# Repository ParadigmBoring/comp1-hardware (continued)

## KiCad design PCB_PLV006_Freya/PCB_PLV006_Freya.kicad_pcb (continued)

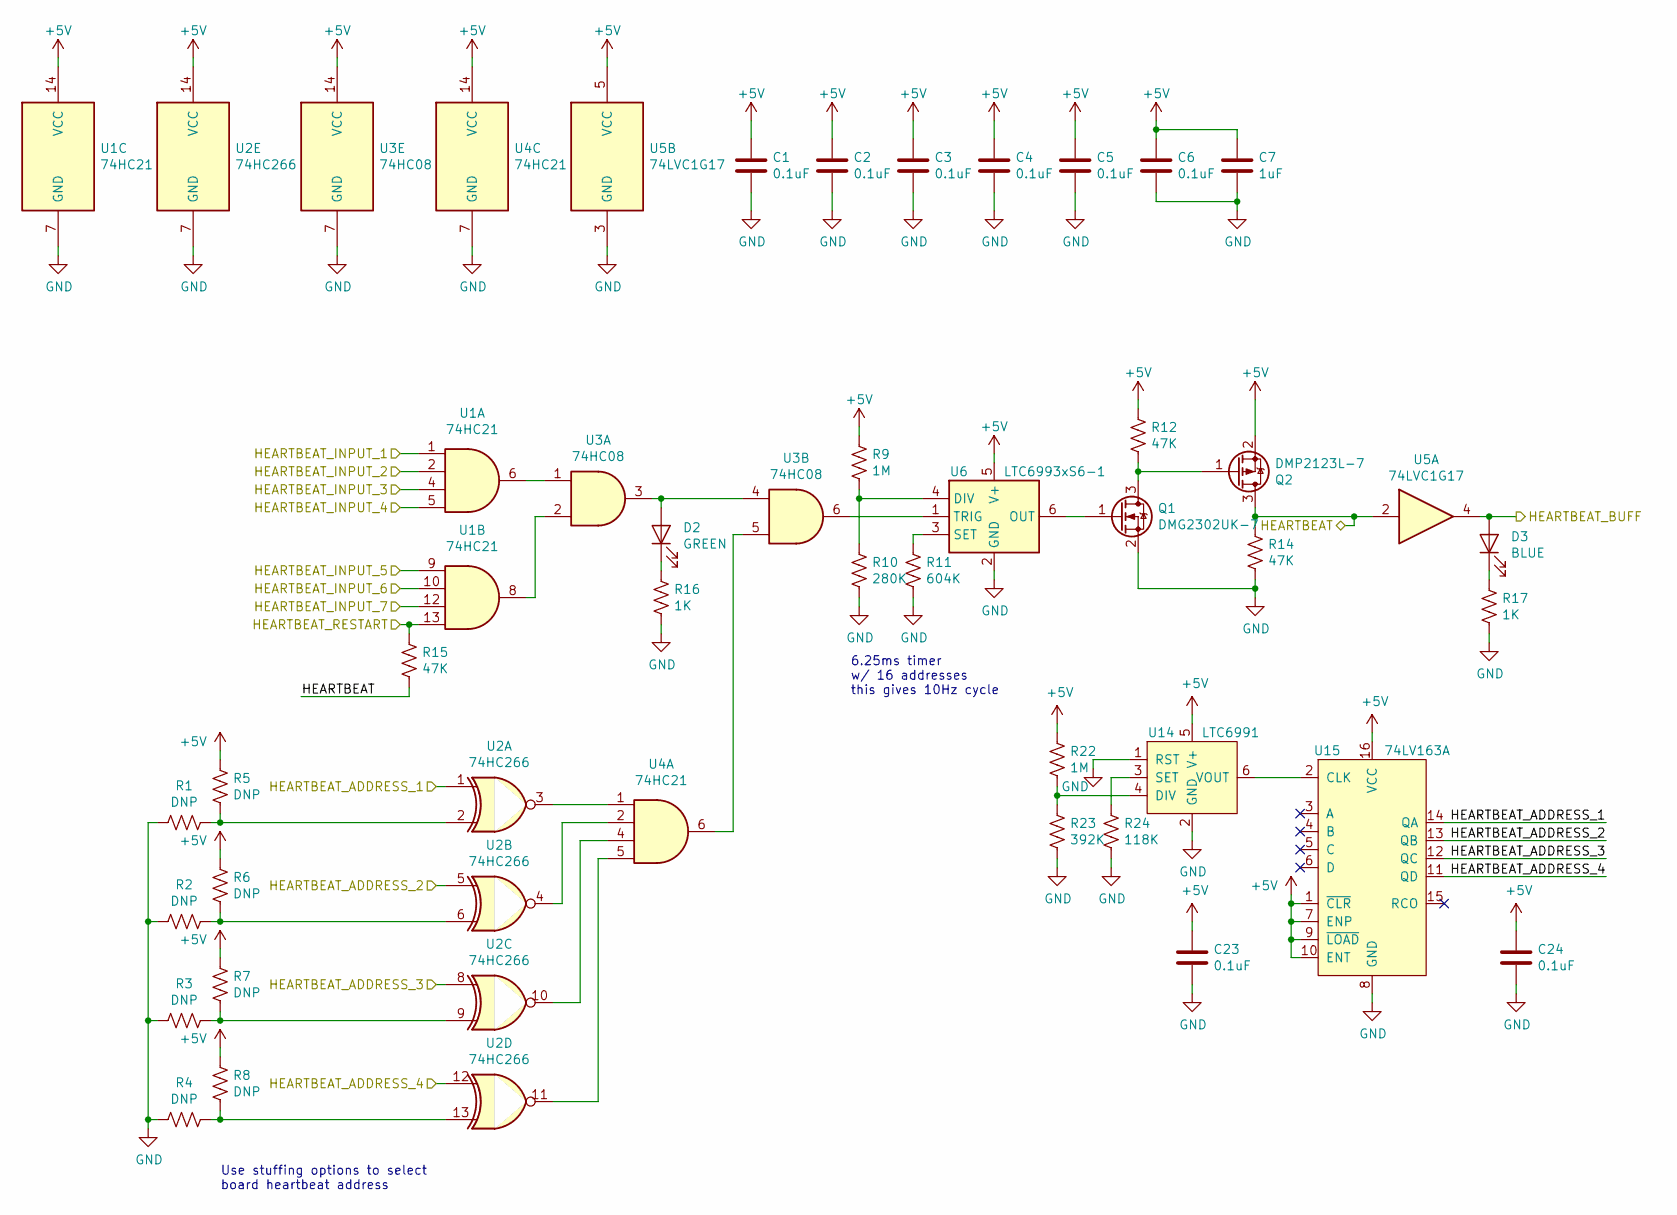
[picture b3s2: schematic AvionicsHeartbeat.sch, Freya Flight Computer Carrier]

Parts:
C1, C2, C3, C4, C5, C6: 0.1uF; C_0603_1608Metric_Pad1.05x0.95mm_HandSolder; Digikey 311-1341-1-ND
C7: 1uF; C_0603_1608Metric_Pad1.05x0.95mm_HandSolder
C23, C24: 0.1uF; C_0603_1608Metric_Pad1.05x0.95mm_HandSolder
D2: GREEN; LED_0805_2012Metric_Pad1.15x1.40mm_HandSolder; Digikey 732-4983-1-ND
D3: BLUE; LED_0805_2012Metric_Pad1.15x1.40mm_HandSolder; Digikey 732-4982-1-ND
Q1: DMG2302UK-7; SOT-23_Handsoldering; Digikey DMG2302UK-7DICT-ND
Q2: DMP2123L-7; SOT-23_Handsoldering; Digikey DMP2123LDICT-ND
R1, R2, R3, R4, R5, R6, R7, R8: DNP; R_0603_1608Metric_Pad1.05x0.95mm_HandSolder
R9, R22: 1M; R_0603_1608Metric_Pad1.05x0.95mm_HandSolder
R10: 280K; R_0603_1608Metric_Pad1.05x0.95mm_HandSolder
R11: 604K; R_0603_1608Metric_Pad1.05x0.95mm_HandSolder
R12, R14, R15: 47K; R_0603_1608Metric_Pad1.05x0.95mm_HandSolder
R16, R17: 1K; R_0603_1608Metric_Pad1.05x0.95mm_HandSolder
R23: 392K; R_0603_1608Metric_Pad1.05x0.95mm_HandSolder
R24: 118K; R_0603_1608Metric_Pad1.05x0.95mm_HandSolder
U1, U4: 74HC21; SOIC-14_3.9x8.7mm_P1.27mm; Digikey 296-31574-1-ND
U2: 74HC266; SOIC-14_3.9x8.7mm_P1.27mm; Digikey 296-31804-1-ND
U3: 74HC08; SOIC-14_3.9x8.7mm_P1.27mm; Digikey 296-14506-1-ND
U5: 74LVC1G17; SOT-23-5_HandSoldering; Digikey 296-11933-1-ND
U6: LTC6993xS6-1; TSOT-23-6; Digikey LTC6993CS6-1#TRMPBFCT-ND
U14: LTC6991; TSOT-23-6_HandSoldering
U15: 74LV163A; SOIC-16_3.9x9.9mm_P1.27mm

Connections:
+5V: C1.1, C2.1, C3.1, C4.1, C5.1, C6.1, C7.1, C23.1, C24.1, Q2.2 (S), R5.1, R6.1, R7.1, R8.1, R9.1, R12.1, R22.1, U1.14 (VCC), U2.14 (VCC), U3.14 (VCC), U4.14 (VCC), U5.5 (VCC), U6.5 (V+), U14.5 (V+), U15.1 (~CLR~), U15.7 (ENP), U15.9 (~LOAD~), U15.10 (ENT), U15.16 (VCC); also elsewhere on the board
/AvionicsHeartbeatTemplate/HEARTBEAT_INPUT_3: U1.4; also elsewhere on the board
/AvionicsHeartbeatTemplate/HEARTBEAT_INPUT_4: U1.5; also elsewhere on the board
/AvionicsHeartbeatTemplate/HEARTBEAT_INPUT_5: U1.9; also elsewhere on the board
/AvionicsHeartbeatTemplate/HEARTBEAT_INPUT_6: U1.10; also elsewhere on the board
/AvionicsHeartbeatTemplate/HEARTBEAT_INPUT_7: U1.12; also elsewhere on the board
/HEARTBEAT_ADDRESS_1: U2.1, U15.14 (QA); also elsewhere on the board
/HEARTBEAT_ADDRESS_2: U2.5, U15.13 (QB); also elsewhere on the board
/HEARTBEAT_ADDRESS_3: U2.8, U15.12 (QC); also elsewhere on the board
/HEARTBEAT_ADDRESS_4: U2.12, U15.11 (QD); also elsewhere on the board
/HEARTBEAT_RESTART: R15.1, U1.1, U1.13; also elsewhere on the board
/MCU_QB_INPUT: U1.2; also elsewhere on the board
/QB: Q2.3 (D), R14.1, R15.2, U5.2; also elsewhere on the board
/QB_BUFF: D3.2 (A), U5.4; also elsewhere on the board
GND: C1.2, C2.2, C3.2, C4.2, C5.2, C6.2, C7.2, C23.2, C24.2, Q1.2 (S), R1.1, R2.1, R3.1, R4.1, R10.2, R11.2, R14.2, R16.2, R17.2, R23.2, R24.2, U1.7 (GND), U2.7 (GND), U3.7 (GND), U4.7 (GND), U5.3 (GND), U6.2 (GND), U14.1 (RST), U14.2 (GND), U15.8 (GND); also elsewhere on the board
unnamed: D2.1 (K), R16.1
unnamed: D2.2 (A), U3.3, U3.4
unnamed: D3.1 (K), R17.1
unnamed: Q1.1 (G), U6.6 (OUT)
unnamed: Q1.3 (D), Q2.1 (G), R12.2
unnamed: R1.2, R5.2, U2.2
unnamed: R2.2, R6.2, U2.6
unnamed: R3.2, R7.2, U2.9
unnamed: R4.2, R8.2, U2.13
unnamed: R9.2, R10.1, U6.4 (DIV)
unnamed: R11.1, U6.3 (SET)
unnamed: R22.2, R23.1, U14.4 (DIV)
unnamed: R24.1, U14.3 (SET)
unnamed: U1.6, U3.1
unnamed: U1.8, U3.2
unnamed: U2.3, U4.1
unnamed: U2.4, U4.2
unnamed: U2.10, U4.4
unnamed: U2.11, U4.5
unnamed: U3.5, U4.6
unnamed: U3.6, U6.1 (TRIG)
unnamed: U14.6 (VOUT), U15.2 (CLK)

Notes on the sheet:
6.25ms timer w/ 16 addresses this gives 10Hz cycle
Use stuffing options to select board heartbeat address

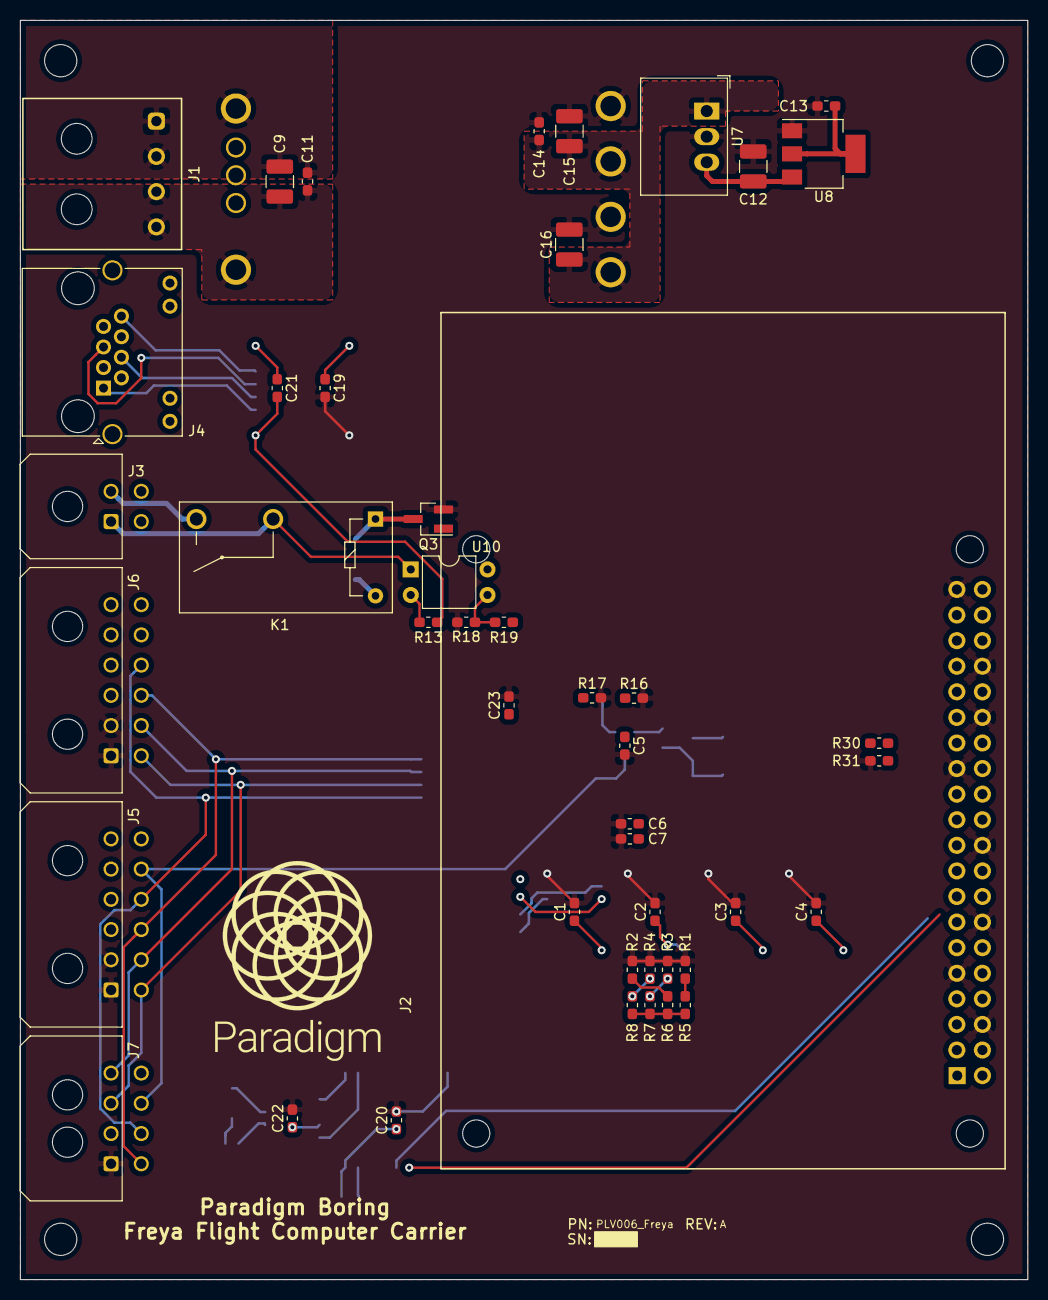
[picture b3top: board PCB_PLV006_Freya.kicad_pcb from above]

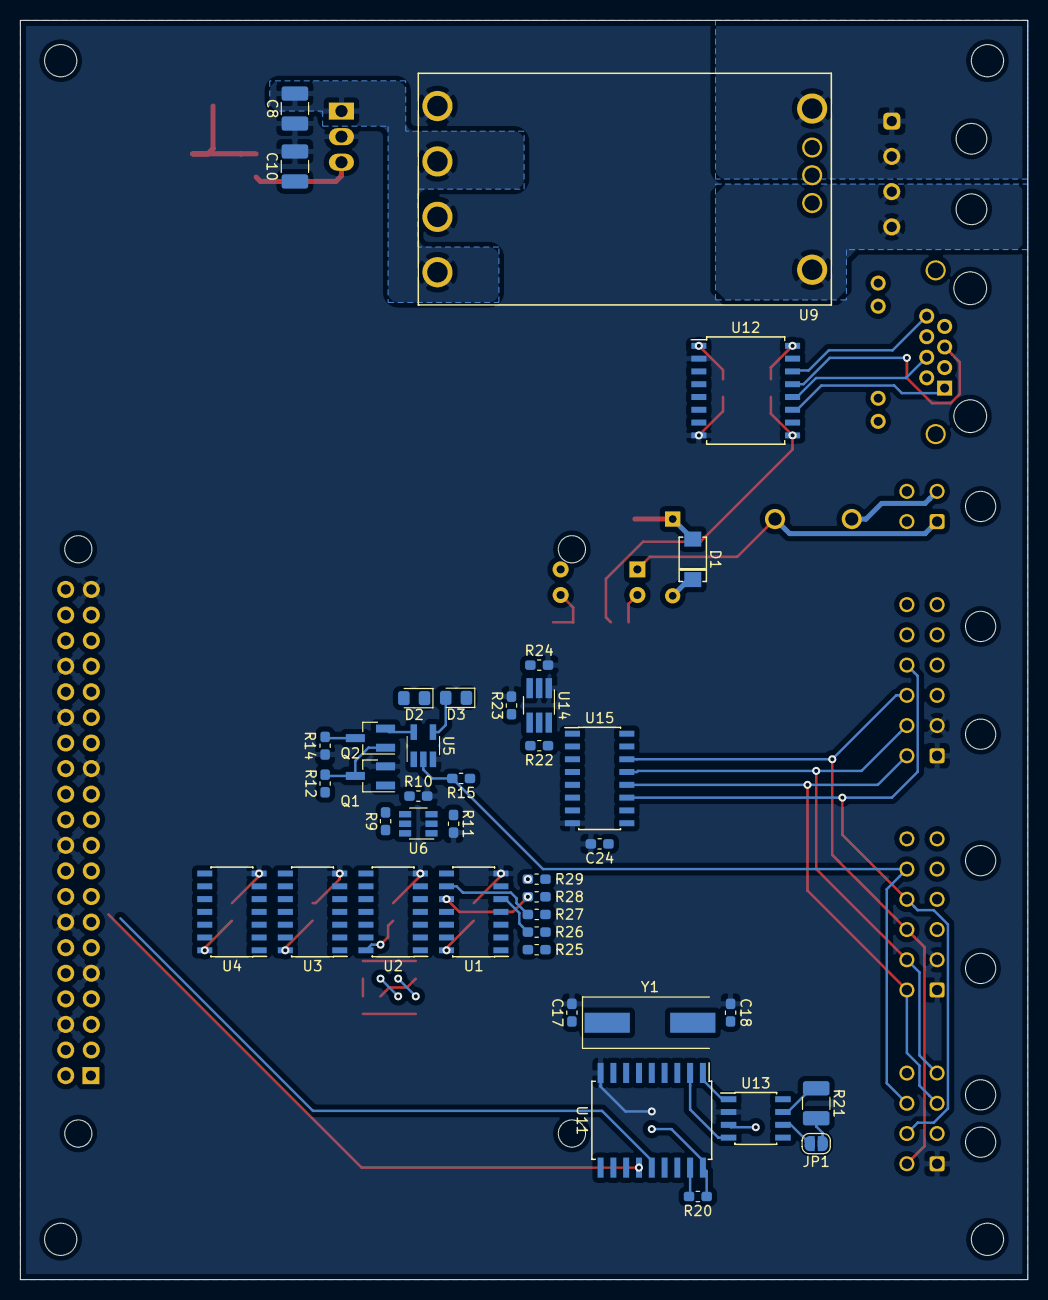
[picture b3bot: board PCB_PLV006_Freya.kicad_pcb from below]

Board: 2 copper layers, 100.0 x 125.0 mm, 86 parts (40 on the bottom side), 68 nets.

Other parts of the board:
J5: NAV; Molex_Micro-Fit_3.0_43045-1200_2x06_P3.00mm_Horizontal
J6: SENSE/ACT; Molex_Micro-Fit_3.0_43045-1200_2x06_P3.00mm_Horizontal
J7: QBI; Molex_Micro-Fit_3.0_43045-0800_2x04_P3.00mm_Horizontal

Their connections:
+24V: J5.3, J5.4, J6.3, J6.4, J7.2; also elsewhere on the board
/CANH: J5.6, J6.6; also elsewhere on the board
/CANL: J5.5, J6.5; also elsewhere on the board
/HEARTBEAT_ADDRESS_1: J5.9, J6.9, J7.5; also elsewhere on the board
/HEARTBEAT_ADDRESS_2: J5.8, J6.8, J7.4; also elsewhere on the board
/HEARTBEAT_ADDRESS_3: J5.7, J6.7, J7.3; also elsewhere on the board
/HEARTBEAT_ADDRESS_4: J5.10, J6.10, J7.6; also elsewhere on the board
/QB: J5.11, J6.11, J7.7; also elsewhere on the board
GND: J5.1, J5.2, J6.1, J6.2, J7.1; also elsewhere on the board

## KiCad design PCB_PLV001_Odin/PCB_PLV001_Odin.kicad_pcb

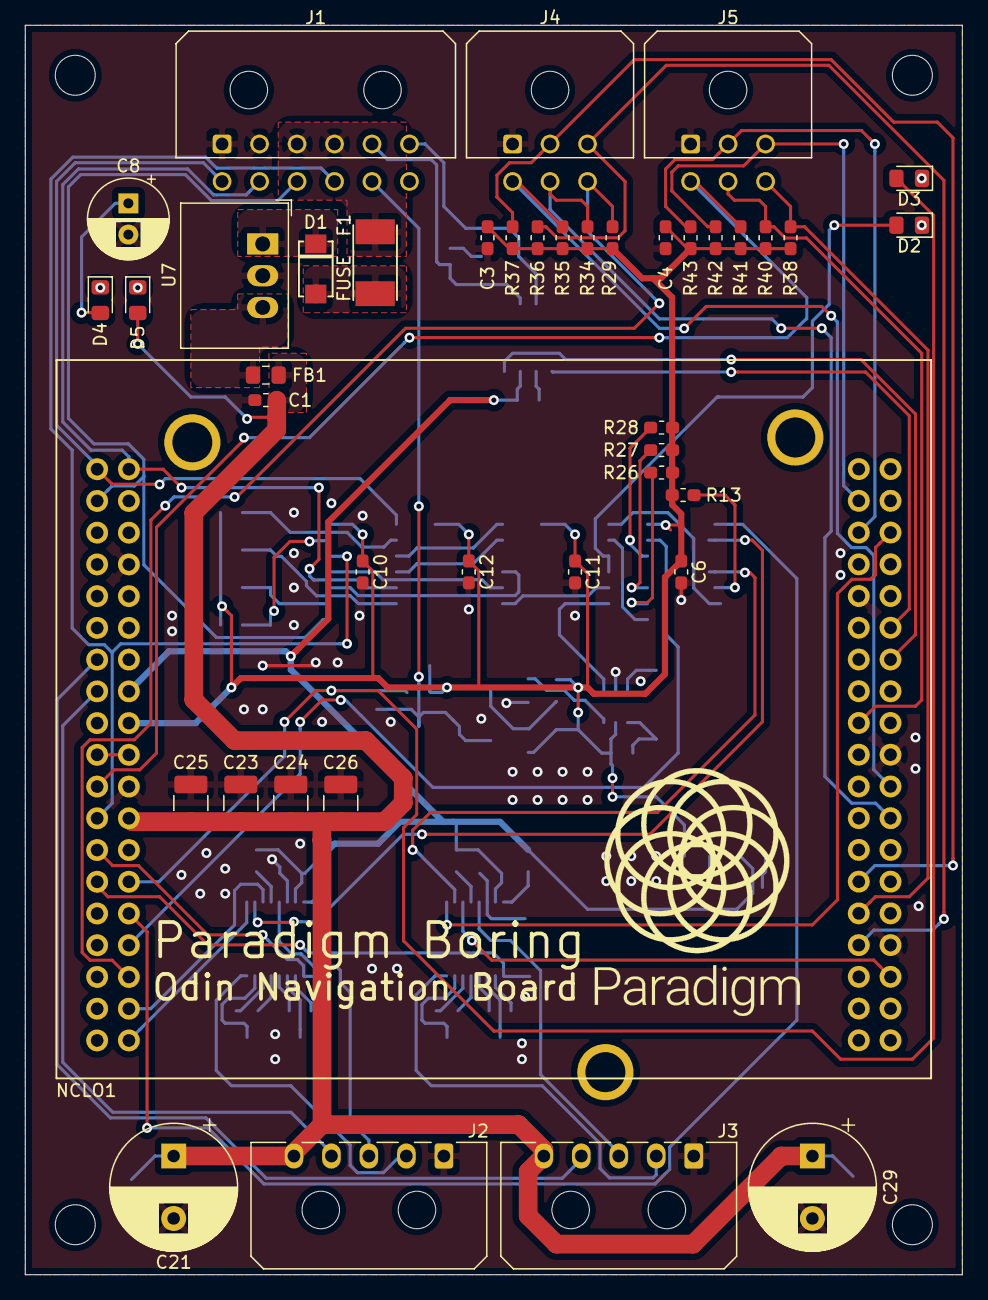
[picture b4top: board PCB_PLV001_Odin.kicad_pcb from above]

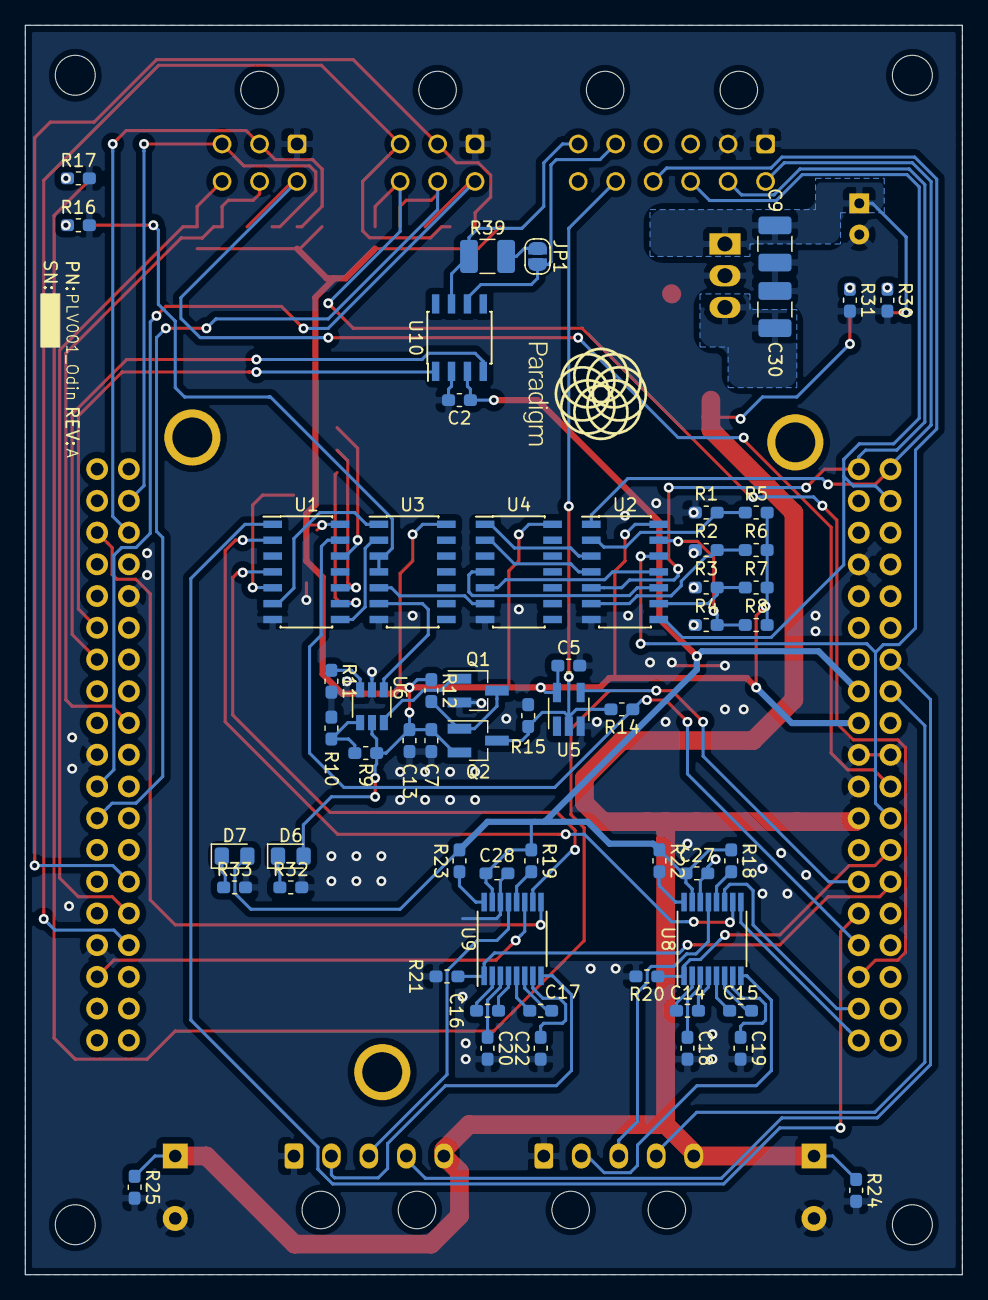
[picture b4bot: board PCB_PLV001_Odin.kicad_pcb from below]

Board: 2 copper layers, 75.0 x 100.0 mm, 101 parts (59 on the bottom side), 88 nets.

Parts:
C1, C2, C3, C4, C5, C6, C10, C11, C12, C13, C14, C15, C16, C17, C18, C19, C20, C22, C27, C28: 0.1uF; C_0603_1608Metric_Pad1.05x0.95mm_HandSolder
C7: 1uF; C_0603_1608Metric_Pad1.05x0.95mm_HandSolder
C8: 47uF; CP_Radial_D6.3mm_P2.50mm
C9, C23, C24, C25, C26, C30: 10uF; C_1210_3225Metric_Pad1.42x2.65mm_HandSolder
C21, C29: 470uF; CP_Radial_D10.0mm_P5.00mm
D1: D_Schottky; DO-221AC
D2: QB_IN; LED_0805_2012Metric_Pad1.15x1.40mm_HandSolder
D3: QB_OUT; LED_0805_2012Metric_Pad1.15x1.40mm_HandSolder
D4: VIN; LED_0805_2012Metric_Pad1.15x1.40mm_HandSolder
D5: 12V; LED_0805_2012Metric_Pad1.15x1.40mm_HandSolder
D6: 5V; LED_0805_2012Metric_Pad1.15x1.40mm_HandSolder
D7: 3V3; LED_0805_2012Metric_Pad1.15x1.40mm_HandSolder
F1: 2A; BelFuse_0679H
FB1: 30ohm@100MHz; L_0805_2012Metric_Pad1.15x1.40mm_HandSolder
J1: PWR/CAN/QB; Molex_Micro-Fit_3.0_43045-1200_2x06_P3.00mm_Horizontal
J2: IMU; Molex_Micro-Fit_3.0_43650-0500_1x05_P3.00mm_Horizontal
J3: INS; Molex_Micro-Fit_3.0_43650-0500_1x05_P3.00mm_Horizontal
J4: ROT1; Molex_Micro-Fit_3.0_43045-0600_2x03_P3.00mm_Horizontal
J5: ROT2; Molex_Micro-Fit_3.0_43045-0600_2x03_P3.00mm_Horizontal
JP1: CAN_TERM; SolderJumper-2_P1.3mm_Open_RoundedPad1.0x1.5mm
NCLO1: NUCLEO-L476RG; ST_Nucleo-64
Q1: DMG2302UK-7; SOT-23_Handsoldering
Q2: DMP2123L-7; SOT-23_Handsoldering
R1, R2, R3, R4, R5, R6, R7, R8: DNP; R_0603_1608Metric_Pad1.05x0.95mm_HandSolder
R9: 1M; R_0603_1608Metric_Pad1.05x0.95mm_HandSolder
R10: 280K; R_0603_1608Metric_Pad1.05x0.95mm_HandSolder
R11: 604K; R_0603_1608Metric_Pad1.05x0.95mm_HandSolder
R12, R14, R15, R20, R21: 47K; R_0603_1608Metric_Pad1.05x0.95mm_HandSolder
R13, R18, R19, R22, R23, R26, R27, R28: 0; R_0603_1608Metric_Pad1.05x0.95mm_HandSolder
R16, R17, R32: 1K; R_0603_1608Metric_Pad1.05x0.95mm_HandSolder
R24, R25: 100K; R_0603_1608Metric_Pad1.05x0.95mm_HandSolder
R29, R34, R35, R36, R37, R38, R40, R41, R42, R43: 10K; R_0603_1608Metric_Pad1.05x0.95mm_HandSolder
R30: 11K; R_0603_1608Metric_Pad1.05x0.95mm_HandSolder
R31: 4.7K; R_0603_1608Metric_Pad1.05x0.95mm_HandSolder
R33: 47; R_0603_1608Metric_Pad1.05x0.95mm_HandSolder
R39: 120; R_1210_3225Metric_Pad1.42x2.65mm_HandSolder
U1, U4: 74HC21; SOIC-14_3.9x8.7mm_P1.27mm
U2: 74HC266; SOIC-14_3.9x8.7mm_P1.27mm
U3: 74HC08; SOIC-14_3.9x8.7mm_P1.27mm
U5: 74LVC1G17; SOT-23-5_HandSoldering
U6: LTC6993xS6-1; TSOT-23-6
U7: R-78B12-2.0; Converter_DCDC_RECOM_R-78B-2.0_THT
U8, U9: MAX3221; TSSOP-16_4.4x5mm_P0.65mm
U10: SN65HVD232; SOIC-8_3.9x4.9mm_P1.27mm

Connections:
+3V3: C2.1, C27.1, C28.1, D7.2, NCLO1.16, R18.1, R19.1, R22.1, R23.1, U8.15, U9.15, U10.3
+5V: C3.1, C4.1, C5.1, C6.1, C7.1, C10.1, C11.1, C12.1, C13.1, D6.2, NCLO1.18, Q2.2, R5.1, R6.1, R7.1, R8.1, R9.1, R12.1, R13.2, R26.2, R27.2, R28.2, R29.2, R34.2, R35.2, R36.2, R37.2, R38.2, R40.2, R41.2, R42.2, R43.2, U1.14, U2.14, U3.14, U4.14, U5.5, U6.5
+12V: C1.1, C21.1, C23.1, C24.1, C25.1, C26.1, C29.1, D5.2, FB1.1, J2.5, J3.5, NCLO1.24, R24.1, R25.1
+24V: C8.1, C9.1, D1.1, D4.2, U7.1
/232_1_VALID: U1.2, U8.10
/232_2_VALID: U1.4, U9.10
/AvionicsHeartbeatTemplate/HEARTBEAT_INPUT_4: R13.1, U1.5
/AvionicsHeartbeatTemplate/HEARTBEAT_INPUT_5: R26.1, U1.9
/AvionicsHeartbeatTemplate/HEARTBEAT_INPUT_6: R27.1, U1.10
/AvionicsHeartbeatTemplate/HEARTBEAT_INPUT_7: R28.1, U1.12
/CANH: J1.6, R39.1, U10.7
/CANL: J1.5, JP1.2, U10.6
/CAN_RX: NCLO1.52, U10.4
/CAN_TX: NCLO1.50, U10.1
/HEARTBEAT: J1.11, Q2.3, R14.2, R15.1, U5.2
/HEARTBEAT_ADDRESS_1: J1.7, NCLO1.1, U2.1
/HEARTBEAT_ADDRESS_2: J1.8, NCLO1.2, U2.5
/HEARTBEAT_ADDRESS_3: J1.9, NCLO1.3, U2.8
/HEARTBEAT_ADDRESS_4: J1.10, NCLO1.23, U2.12
/HEARTBEAT_BUFF: D3.2, NCLO1.28, U5.4
/HEARTBEAT_RESTART: NCLO1.32, R14.1, U1.13
/IMU_TOV: J2.4, NCLO1.15
/INS_PPS: J3.4, NCLO1.13
/MCU_QB_INPUT: NCLO1.30, U1.1
/ROT1_PPS1: J4.2, NCLO1.65, R37.1
/ROT1_PPS2: J4.3, NCLO1.69, R36.1
/ROT1_PPS3: J4.4, NCLO1.60, R35.1
/ROT1_PPS4: J4.5, NCLO1.62, R34.1
/ROT1_PPS5: J4.6, NCLO1.34, R29.1
/ROT2_PPS1: J5.2, NCLO1.43, R43.1
/ROT2_PPS2: J5.3, NCLO1.41, R42.1
/ROT2_PPS3: J5.4, NCLO1.21, R41.1
/ROT2_PPS4: J5.5, NCLO1.55, R40.1
/ROT2_PPS5: J5.6, NCLO1.67, R38.1
/Transceivers/232_1_RX: J2.2, U8.8
/Transceivers/232_1_TX: J2.3, U8.13
/Transceivers/232_2_RX: J3.2, U9.8
/Transceivers/232_2_TX: J3.3, U9.13
/UART1_RX: NCLO1.38, U8.9
/UART1_TX: NCLO1.36, U8.11
/UART2_RX: NCLO1.44, U9.9
/UART2_TX: NCLO1.72, U9.11
/VIN: F1.2, J1.3, J1.4
/n232_1_EN: NCLO1.25, R20.1, U8.1
/n232_2_EN: NCLO1.27, R21.1, U9.1
GND: C1.2, C2.2, C3.2, C4.2, C5.2, C6.2, C7.2, C8.2, C9.2, C10.2, C11.2, C12.2, C13.2, C18.2, C19.2, C20.2, C21.2, C22.2, C23.2, C24.2, C25.2, C26.2, C27.2, C28.2, C29.2, C30.2, J1.1, J1.2, J2.1, J3.1, J4.1, J5.1, NCLO1.8, NCLO1.19, NCLO1.20, NCLO1.22, NCLO1.47, NCLO1.58, NCLO1.70, Q1.2, R1.1, R2.1, R3.1, R4.1, R10.2, R11.2, R15.2, R16.2, R17.2, R20.2, R21.2, R24.2, R25.2, R30.2, R31.2, R32.2, R33.2, U1.7, U2.7, U3.7, U4.7, U5.3, U6.2, U7.2, U8.14, U9.14, U10.2
unnamed: C14.1, U8.2
unnamed: C14.2, U8.4
unnamed: C15.1, U8.5
unnamed: C15.2, U8.6
unnamed: C16.1, U9.2
unnamed: C16.2, U9.4
unnamed: C17.1, U9.5
unnamed: C17.2, U9.6
unnamed: C18.1, U8.3
unnamed: C19.1, U8.7
unnamed: C20.1, U9.3
unnamed: C22.1, U9.7
unnamed: C30.1, FB1.2, U7.3
unnamed: D1.2, F1.1
unnamed: D2.1, R16.1
unnamed: D2.2, U3.3, U3.4
unnamed: D3.1, R17.1
unnamed: D4.1, R30.1
unnamed: D5.1, R31.1
unnamed: D6.1, R32.1
unnamed: D7.1, R33.1
unnamed: JP1.1, R39.2
unnamed: Q1.1, U6.6
unnamed: Q1.3, Q2.1, R12.2
unnamed: R1.2, R5.2, U2.2
unnamed: R2.2, R6.2, U2.6
unnamed: R3.2, R7.2, U2.9
unnamed: R4.2, R8.2, U2.13
unnamed: R9.2, R10.1, U6.4
unnamed: R11.1, U6.3
unnamed: R18.2, U8.12
unnamed: R19.2, U9.12
unnamed: R22.2, U8.16
unnamed: R23.2, U9.16
unnamed: U1.6, U3.1
unnamed: U1.8, U3.2
unnamed: U2.3, U4.1
unnamed: U2.4, U4.2
unnamed: U2.10, U4.4
unnamed: U2.11, U4.5
unnamed: U3.5, U4.6
unnamed: U3.6, U6.1

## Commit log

2020-12-18 Beyla PCB for review
2020-12-24 Odin routing
2020-12-27 Some Beyla Routing Changes
    - Q1 and U8 overlap fixed
    - Decoupling capacitors moved
    - Transistor symbol fix in QB template schematic
2020-12-28 Fix transistors in heartbeat circuits
2020-12-29 Odin Silk, finish Yggdrasil component selection
2020-12-29 Add 3D models for connectors to Odin
2020-12-29 Beyla timer IC layout changes
2020-12-30 Make Odin pass DRC, finish Yggdrasil
2020-12-30 Beyla Layout Fixes
    Fixed the problems with the first layout.
2020-12-30 Beyla Layout Fixes v2
    Fixed some overlapping footprints.
2020-12-30 Fix Beyla footprint overlap
2021-01-01 Change power traces, clean up grounds on Beyla
2021-01-02 Added 3D models to Beyla
2021-01-02 Updated 3D models
2021-01-02 Finalized Beyla 3D models
2021-01-08 Start Freya
2021-01-08 Work on Freya
2021-01-12 Idek anymore
2021-01-12 Fix library and add act
2021-01-12 Freya stuff
2021-01-14 Done with Freya for FDP
2021-01-14 Finish schematic
2021-01-16 Done
2021-02-16 Beyla Voltage Regulator Fix
2021-03-22 Updated Yggdrasil layout/routing (first draft)
2021-03-29 New Odin Routing
2021-03-31 Implementing feedback from Jasper (p.1)
    - Trace between F1 and D1 changed to 1.000mm
    - Moved Umbilical_V+ to left edge of board, changed trace width to 2.5mm. 1mm trace still used between pads on U11 and from U11 to R50.
    - Moved the 3.3V trace that supplies the components on the bottom right corner
    - Moved some of the traces on the right side. Long-running overlap should be minimized here now.
    - Added a ground plane to the back and cleaned up some of the random traces that I had before. I added keep-outs to get rid of weird or floating fills, and I threw vias in some places to connect the 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
    - Silkscreen update not started, to
2021-04-02 Schematic clean up, addition of fan actuation, addition of tvs diodes in control of SSRs
2021-04-02 Schematic Clean up, Fan Actuation, SSR actuation sch fix
2021-04-02 Schematic fix of actuator drivers
2021-04-07 Silkscreen First Pass
2021-04-20 Yggdrasil Minor Routing Fixes
    Just cleaned up some unequal trace spacing in places
2021-05-04 Yggdrasil Nucleo Changes
    Minor routing changes to accommodate Nucleo footprint and model update
